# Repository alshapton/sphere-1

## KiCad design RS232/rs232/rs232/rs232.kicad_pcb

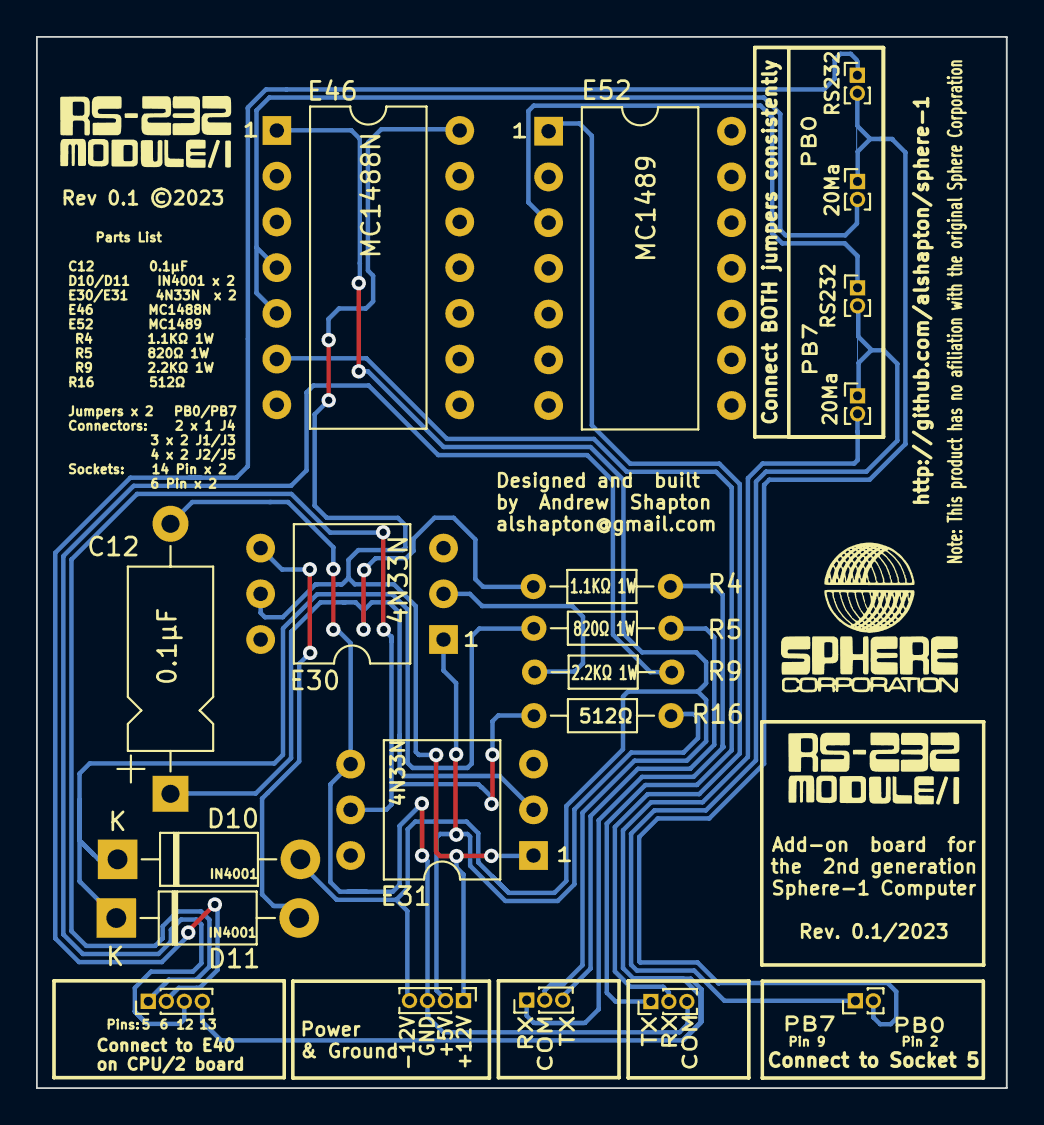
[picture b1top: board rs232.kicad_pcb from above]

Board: 2 copper layers, 53.9 x 58.4 mm, 20 parts (0 on the bottom side), 15 nets.

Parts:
C12: CK-104; CP_Axial_L10.0mm_D4.5mm_P15.00mm_Horizontal
D10, D11: 1N4001; D_DO-41_SOD81_P10.16mm_Horizontal
E30, E31: 4N33N; DIP-6_W10.16mm
E46: MC1488N; DIP-14_W10.16mm
E52: MC1489; DIP-14_W10.16mm
J1, J3: Conn_01x03_Pin; PinHeader_1x03_P1.00mm_Vertical
J2, J5: Conn_01x04_Pin; PinHeader_1x04_P1.00mm_Vertical
J4: Conn_01x02_Pin; PinHeader_1x02_P1.00mm_Vertical
R4: 1.1 kOhm 1W; R_Axial_DIN0204_L3.6mm_D1.6mm_P7.62mm_Horizontal
R5: 820 Ohm 1W; R_Axial_DIN0204_L3.6mm_D1.6mm_P7.62mm_Horizontal
R9: 2 kOhm ¼W; R_Axial_DIN0204_L3.6mm_D1.6mm_P7.62mm_Horizontal
R16: 512 Ohm ¼W; R_Axial_DIN0204_L3.6mm_D1.6mm_P7.62mm_Horizontal
TSC1, TSC2, TSC3, TSC4: PinHeader_1x02_P1.00mm_Vertical

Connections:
unnamed: C12.1, E31.2 (C), R4.1
unnamed: D10.2 (A), E46.1 (V_{CC}-), J1.2, J2.4
unnamed: D10.1 (K), D11.1 (K), R5.1
unnamed: D11.2 (A), E30.4 (E)
unnamed: E30.1 (A), J2.2, R16.2
unnamed: E30.2 (C), R9.1
unnamed: E30.5 (C), E31.1 (A), E46.14 (V_{CC}+), J2.1
unnamed: C12.2, E31.4 (E), J2.3, J3.3
unnamed: E46.4 (2A), E46.5 (2B)
unnamed: E46.6 (2Y), J3.1
unnamed: E52.1 (1A), J3.2
unnamed: J1.1, R4.2
unnamed: J1.3, R5.2
unnamed: E31.5 (C), J5.1, R16.1
unnamed: J5.3, R9.2

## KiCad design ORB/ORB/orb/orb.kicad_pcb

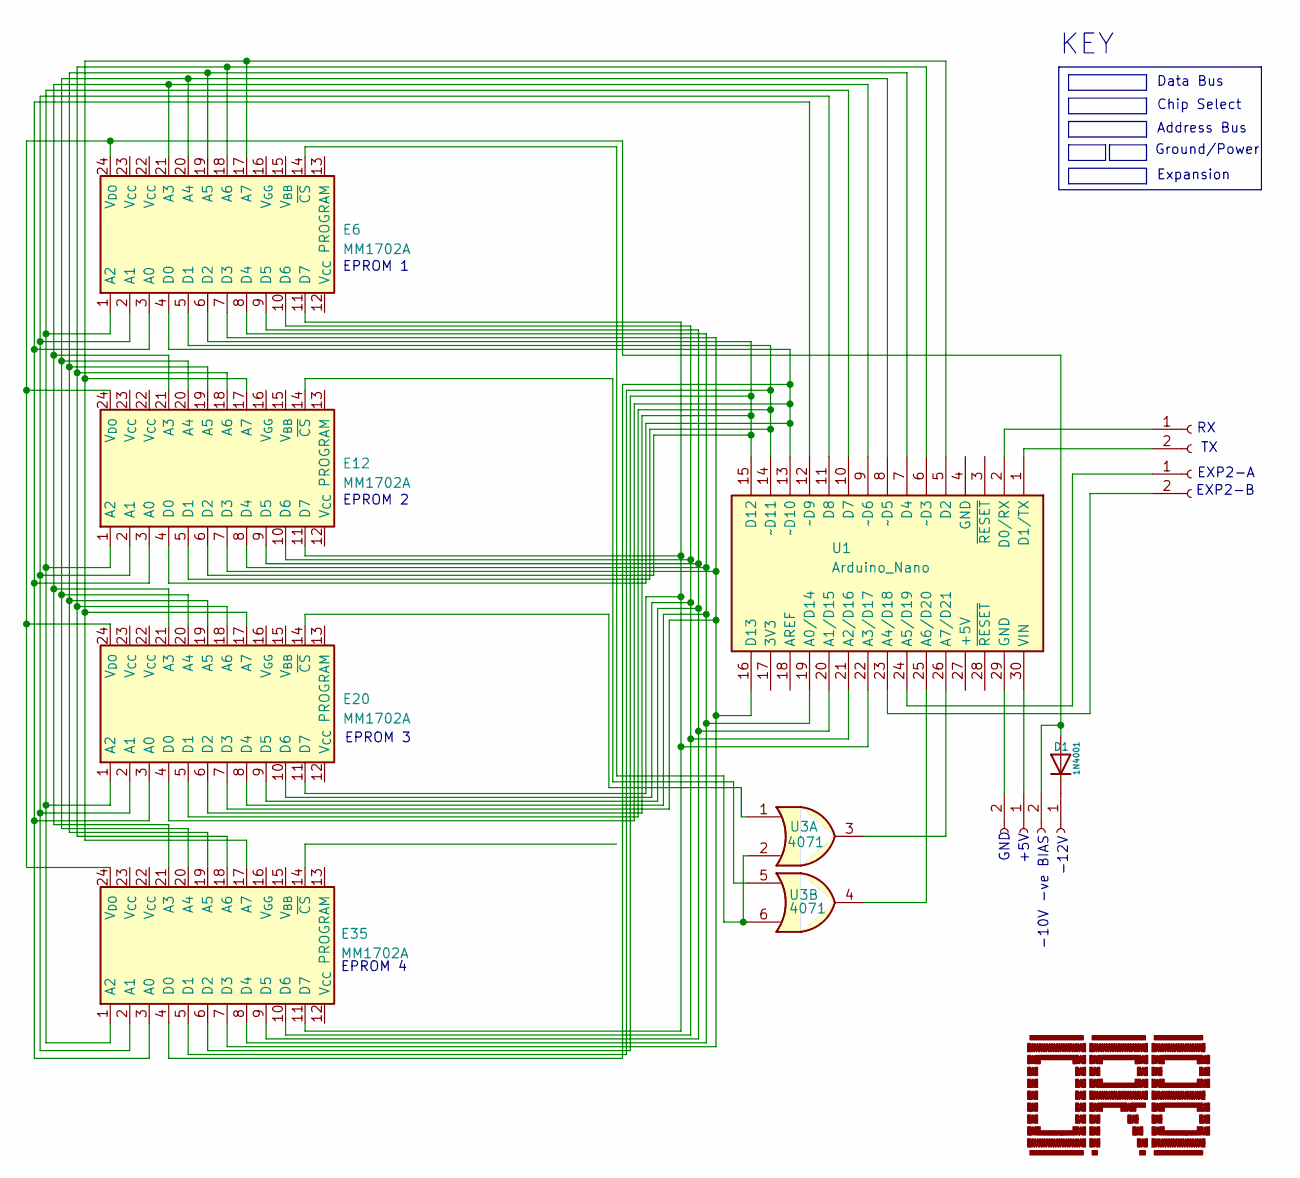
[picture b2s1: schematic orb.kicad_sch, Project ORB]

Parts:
D1: 1N4001; D_DO-41_SOD81_P10.16mm_Horizontal
E6, E12, E20, E35: MM1702A; DIP-24_W10.16mm_Socket
J1, J2, J3, J4: Conn_01x02_Socket; PinHeader_1x02_P1.00mm_Vertical
U1: Arduino_Nano
U3: 4071; PinSocket_2x07_P1.27mm_Vertical

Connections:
unnamed: D1.2 (A), E6.24 (V_{DO}), E12.24 (V_{DO}), E20.24 (V_{DO}), E35.24 (V_{DO}), J4.2
unnamed: D1.1 (K), J4.1
unnamed: E6.14 (~CS), U3.2, U3.6
unnamed: E6.3 (A0), E12.3 (A0), E20.3 (A0), E35.3 (A0), U1.12 (~D9)
unnamed: E6.2 (A1), E12.2 (A1), E20.2 (A1), E35.2 (A1), U1.11 (D8)
unnamed: E6.1 (A2), E12.1 (A2), E20.1 (A2), E35.1 (A2), U1.10 (D7)
unnamed: E6.21 (A3), E12.21 (A3), E20.21 (A3), E35.21 (A3), U1.9 (~D6)
unnamed: E6.20 (A4), E12.20 (A4), E20.20 (A4), E35.20 (A4), U1.8 (~D5)
unnamed: E6.19 (A5), E12.19 (A5), E20.19 (A5), E35.19 (A5), U1.7 (D4)
unnamed: E6.18 (A6), E12.18 (A6), E20.18 (A6), E35.18 (A6), U1.6 (~D3)
unnamed: E6.17 (A7), E12.17 (A7), E20.17 (A7), E35.17 (A7), U1.5 (D2)
unnamed: E6.4 (D0), E12.4 (D0), E20.4 (D0), E35.4 (D0), U1.13 (~D10)
unnamed: E6.5 (D1), E12.5 (D1), E20.5 (D1), E35.5 (D1), U1.14 (~D11)
unnamed: E6.6 (D2), E12.6 (D2), E20.6 (D2), E35.6 (D2), U1.15 (D12)
unnamed: E6.7 (D3), E12.7 (D3), E20.7 (D3), E35.7 (D3), U1.16 (D13)
unnamed: E6.8 (D4), E12.8 (D4), E20.8 (D4), E35.8 (D4), U1.19 (A0/D14)
unnamed: E6.9 (D5), E12.9 (D5), E20.9 (D5), E35.9 (D5), U1.20 (A1/D15)
unnamed: E6.10 (D6), E12.10 (D6), E20.10 (D6), E35.10 (D6), U1.21 (A2/D16)
unnamed: E6.11 (D7), E12.11 (D7), E20.11 (D7), E35.11 (D7), U1.22 (A3/D17)
unnamed: E12.14 (~CS), U3.5
unnamed: E20.14 (~CS), U3.1
unnamed: J1.1, U1.30 (VIN)
unnamed: J1.2, U1.29 (GND)
unnamed: J2.1, U1.2 (D0/RX)
unnamed: J2.2, U1.1 (D1/TX)
unnamed: J3.1, U1.24 (A5/D19)
unnamed: J3.2, U1.23 (A4/D18)
unnamed: U1.25 (A6/D20), U3.4
unnamed: U1.26 (A7/D21), U3.3

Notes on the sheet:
EPROM 2
-12V
-10V -ve BIAS
Data Bus
KEY
EPROM 3
EXP2-A
EXP2-B
Expansion
GND
Address Bus
EPROM 4
Ground/Power
EPROM 1
Chip Select
+5V

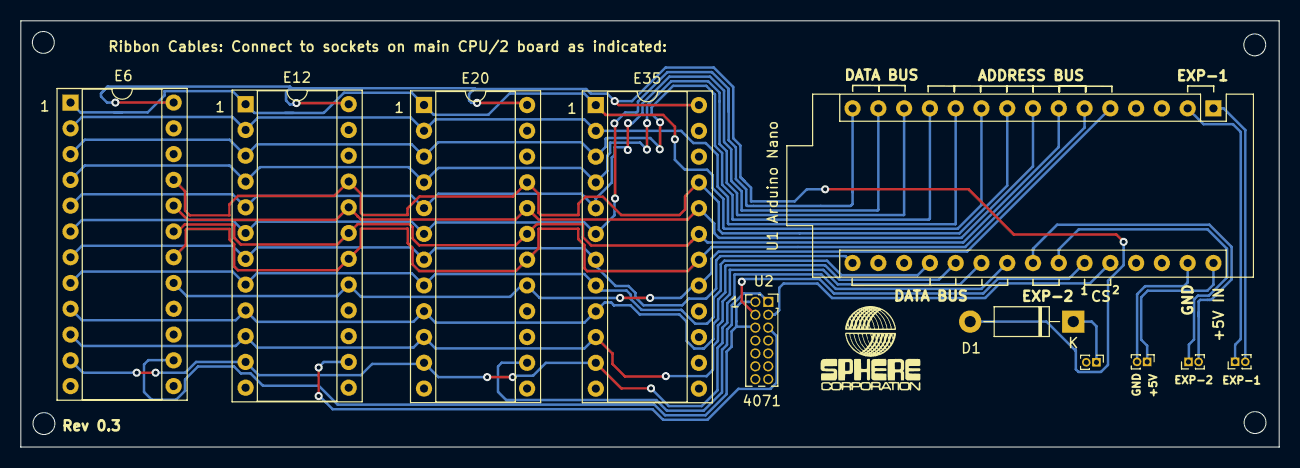
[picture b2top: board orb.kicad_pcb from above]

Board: 2 copper layers, 124.0 x 42.0 mm, 11 parts (0 on the bottom side), 29 nets.

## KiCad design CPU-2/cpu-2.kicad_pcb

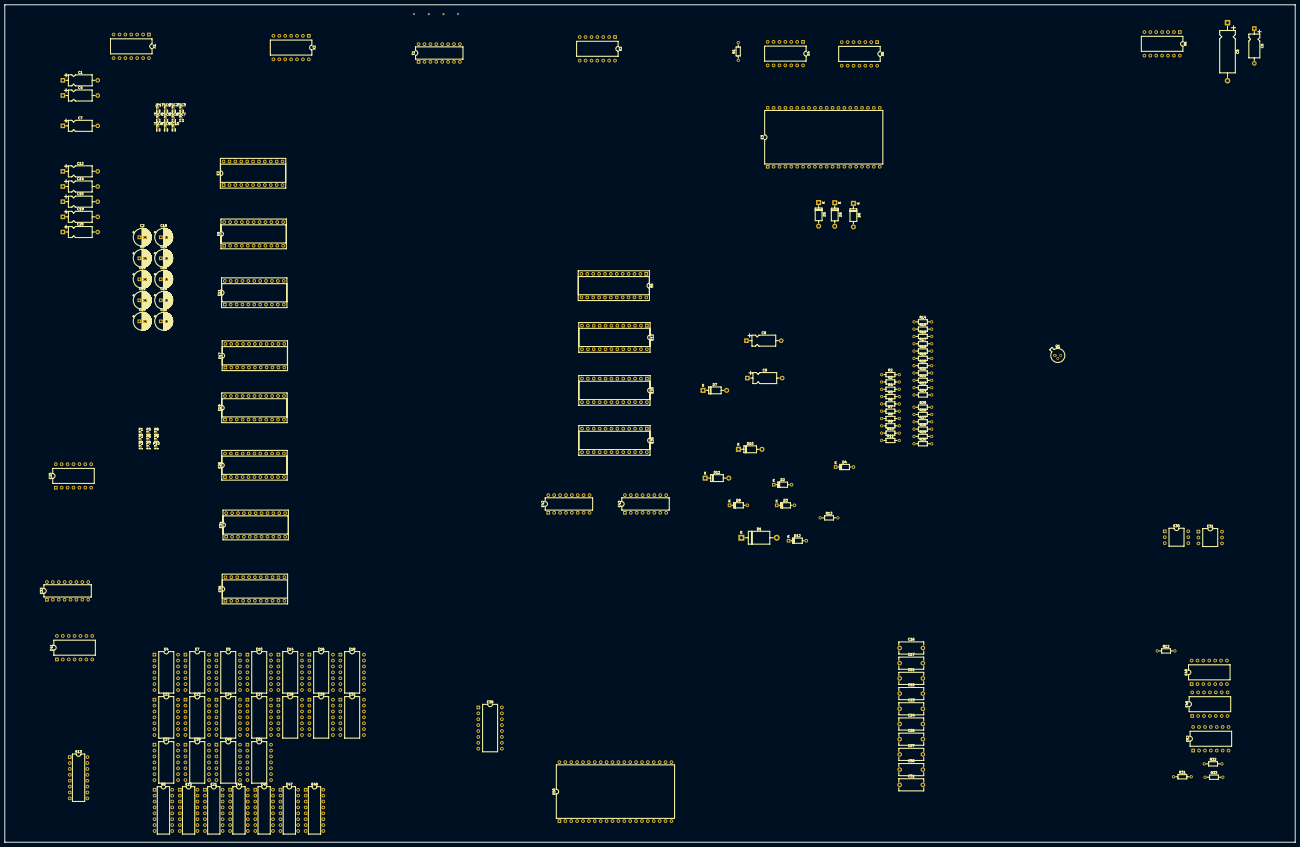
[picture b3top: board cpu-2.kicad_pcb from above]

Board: 2 copper layers, 556.0 x 360.8 mm, 156 parts (0 on the bottom side), 189 nets, no tracks yet.

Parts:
C1, C4, C6, C7, C8, C9, C12, C14, C15, C19, C20: CK-104; CP_Axial_L10.0mm_D4.5mm_P15.00mm_Horizontal
C2: _{EK47/16}; CP_Radial_D7.5mm_P2.50mm
C3, C10, C11, C13, C18, C25, C28, C29, C32: EK47/16; CP_Radial_D7.5mm_P2.50mm
C5: Tantalum Capacitor; CP_Axial_L18.0mm_D6.5mm_P25.00mm_Horizontal
C16: DDM-103'; C_Disc_D10.5mm_W5.0mm_P10.00mm
C17, C22, C23: DDM-103; C_Disc_D10.5mm_W5.0mm_P10.00mm
C21, C27, C31: DD-101; C_Disc_D10.5mm_W5.0mm_P10.00mm
C24, C30: DD-680; C_Disc_D10.5mm_W5.0mm_P10.00mm
C26: _{DDM-103'}; C_Disc_D10.5mm_W5.0mm_P10.00mm
D1: 1N5225B; D_DO-201AE_P15.24mm_Horizontal
D2, D3, D4, D9, D12: 1N914; D_DO-35_SOD27_P7.62mm_Horizontal
D5, D6, D7, D8, D10, D11: 1N4001; D_DO-41_SOD81_P10.16mm_Horizontal
E1, E33: DM8098N; DIP-16_W7.62mm
E2, E5, E11, E17, E19, E26, E34, E36: TMS4030; DIP-22_W10.16mm_Socket
E3: MC6820; DIP-40_W25.4mm
E4, E24: SN7420N; DIP-14_W10.16mm
E6, E12, E20, E35: MM1702A; DIP-24_W10.16mm_Socket
E7, E22, E27: SN7493N; DIP-14_W10.16mm
E8, E45: DM9602N; DIP-16_W7.62mm
E9, E37: SN7474N; DIP-14_W10.16mm
E10, E16, E23: SN7402N; DIP-14_W10.16mm
E13: SN7442N; DIP-16_W7.62mm
E14, E18: SN7411N; DIP-14_W10.16mm
E15, E21, E44, E47, E48: DM8097N; DIP-16_W7.62mm
E25: (SPARE); DIP-14_W10.16mm
E28: SN7408N; DIP-14_W10.16mm
E29: SN7404N; DIP-14_W10.16mm
E30, E31: 4N33N; DIP-6_W10.16mm
E32, E39: SN7400N; DIP-14_W10.16mm
E38: SN74123N; DIP-16_W10.16mm
E40, E41: SN7405N; DIP-14_W10.16mm
E42, E43: DM8833N; DIP-16_W7.62mm
E46: MC1488N; DIP-14_W10.16mm
E49: SN7486N; DIP-14_W10.16mm
E50: MC6800; DIP-40_W25.4mm
E51: MPQ6842; DIP-14_W10.16mm
E52: MC1489; DIP-14_W10.16mm
JP1: Jumper_Open; PinHeader_1x02_P1.00mm_Vertical
P1, P2, P3, P5, P6, P7, P8, P9, P10: PinHeader_1x01_P1.00mm_Vertical
Q1: 2N2369A; TO-18-3_Lens
R1: 100 Ohm ¼W; R_Axial_DIN0204_L3.6mm_D1.6mm_P7.62mm_Horizontal
R2, R3: 36 kOhm ¼W; R_Axial_DIN0204_L3.6mm_D1.6mm_P7.62mm_Horizontal
R4: 1.1 kOhm 1W; R_Axial_DIN0204_L3.6mm_D1.6mm_P7.62mm_Horizontal
R5: 820 Ohm 1W; R_Axial_DIN0204_L3.6mm_D1.6mm_P7.62mm_Horizontal
R6: 130 Ohm 2W; R_Axial_DIN0204_L3.6mm_D1.6mm_P7.62mm_Horizontal
R7, R8, R18, R20, R29: 3.3 kOhm ¼W; R_Axial_DIN0204_L3.6mm_D1.6mm_P7.62mm_Horizontal
R9: 2 kOhm ¼W; R_Axial_DIN0204_L3.6mm_D1.6mm_P7.62mm_Horizontal
R10: 15 kOhm ¼W; R_Axial_DIN0204_L3.6mm_D1.6mm_P7.62mm_Horizontal
R11: 27.1 kOhm ¼W; R_Axial_DIN0204_L3.6mm_D1.6mm_P7.62mm_Horizontal
R12: 11 kOhm ¼W; R_Axial_DIN0204_L3.6mm_D1.6mm_P7.62mm_Horizontal
R13: 33 kOhm ¼W; R_Axial_DIN0204_L3.6mm_D1.6mm_P7.62mm_Horizontal
R14: Resistor (R14); R_Axial_DIN0204_L3.6mm_D1.6mm_P7.62mm_Horizontal
R15, R33: 470 Ohm ¼W; R_Axial_DIN0204_L3.6mm_D1.6mm_P7.62mm_Horizontal
R16: 512 Ohm ¼W; R_Axial_DIN0204_L3.6mm_D1.6mm_P7.62mm_Horizontal
R17, R19, R31, R32: 1 kOhm ¼W; R_Axial_DIN0204_L3.6mm_D1.6mm_P7.62mm_Horizontal
R21, R28, R30: 10 kOhm ¼W; R_Axial_DIN0204_L3.6mm_D1.6mm_P7.62mm_Horizontal
R22, R25: 22 Ohm ¼W; R_Axial_DIN0204_L3.6mm_D1.6mm_P7.62mm_Horizontal
R23, R26: 10 Ohm ¼W; R_Axial_DIN0204_L3.6mm_D1.6mm_P7.62mm_Horizontal
R24, R27: 4.7 kOhm ¼W; R_Axial_DIN0204_L3.6mm_D1.6mm_P7.62mm_Horizontal
TSC1, TSC2, TSC3, TSC4, TSC5, TSC6, TSC7, TSC8, TSC9, TSC10: PinHeader_1x02_P1.00mm_Vertical
X1, X2, X3, X4, X5, X6: 14-Pin Socket; DIP-14_W10.16mm

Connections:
+5V: C5.1, C28.1, D12.1 (K), E2.11 (V_{CC}), E3.25 (ENABLE), E4.7 (GND), E5.11 (V_{CC}), E8.3 (CLR1), E8.13 (CLR2), E9.1 (1~CLR), E9.4 (1~PRE), E9.10 (2~PRE), E9.12 (2D), E10.7 (GND), E11.11 (V_{CC}), E14.13 (1C), E15.9 (Y4), E16.7 (GND), E17.11 (V_{CC}), E18.7 (GND), E19.11 (V_{CC}), E24.2 (1B), E24.7 (GND), E26.11 (V_{CC}), E30.1 (A), E32.7 (GND), E32.12 (4B), E34.11 (V_{CC}), E36.11 (V_{CC}), E37.1 (1~CLR), E37.4 (1~PRE), E37.10 (2~PRE), E37.12 (2D), E38.2 (1B), E38.3 (1~CLR), E38.10 (2B), E38.11 (2~CLR), E41.7 (GND), E45.3 (CLR1), E45.5 (A1), E45.11 (A2), E45.13 (CLR2), E49.7 (GND), E49.13 (4B), E50.8 (V_{CC}), E51.5, E51.10, R2.2, R3.1, R7.1, R10.2, R11.2, R12.2, R13.2, R14.2, R15.1, R16.2, R17.2, R18.1, R19.2, R28.1, R31.1, R32.2, R33.1, X1.14, X5.7, X5.14, X6.6, X6.7, X6.13, X6.14
+12V: C3.1, C10.1, C11.1, C13.1, C18.1, D9.1 (K), E2.18 (V_{DD}), E5.18 (V_{DD}), E11.18 (V_{DD}), E17.18 (V_{DD}), E19.18 (V_{DD}), E26.18 (V_{DD}), E30.5 (C), E31.1 (A), E34.18 (V_{DD}), E36.18 (V_{DD}), E46.14 (V_{CC}+), R6.1, X6.10
-3V3: C2.1, D1.2 (A2), D3.2 (A), E2.1 (V_{BB}), E5.1 (V_{BB}), E11.1 (V_{BB}), E17.1 (V_{BB}), E19.1 (V_{BB}), E26.1 (V_{BB}), E34.1 (V_{BB}), E36.1 (V_{BB}), X6.4, X6.11
-12V: D10.2 (A), E46.1 (V_{CC}-)
/A_{0}: E2.8 (A0), E5.8 (A0), E6.3 (A0), E11.8 (A0), E12.3 (A0), E16.3 (1B), E17.8 (A0), E19.8 (A0), E20.3 (A0), E21.13 (Y6), E26.8 (A0), E34.8 (A0), E35.3 (A0), E36.8 (A0), X2.8
/A_{1}: E2.9 (A1), E5.9 (A1), E6.2 (A1), E11.9 (A1), E12.2 (A1), E16.2 (1A), E17.9 (A1), E19.9 (A1), E20.2 (A1), E21.9 (Y4), E26.9 (A1), E34.9 (A1), E35.2 (A1), E36.9 (A1), X2.9
/A_{2}: E2.10 (A2), E5.10 (A2), E6.1 (A2), E11.10 (A2), E12.1 (A2), E17.10 (A2), E19.10 (A2), E20.1 (A2), E21.7 (Y3), E24.9 (2A), E26.10 (A2), E34.10 (A2), E35.1 (A2), E36.10 (A2), X2.1
/A_{3}: E2.13 (A3), E5.13 (A3), E6.21 (A3), E10.5 (2A), E11.13 (A3), E12.21 (A3), E17.13 (A3), E19.13 (A3), E20.21 (A3), E21.2 (A1), E21.3 (Y1), E22.14 (CKA), E26.13 (A3), E27.11 (Q_{D}), E34.13 (A3), E35.21 (A3), E36.13 (A3), X2.3
/A_{4}: E2.14 (A4), E5.14 (A4), E6.20 (A4), E10.8 (3A), E11.14 (A4), E12.20 (A4), E17.14 (A4), E19.14 (A4), E20.20 (A4), E21.11 (Y5), E26.14 (A4), E34.14 (A4), E35.20 (A4), E36.14 (A4), X2.2
/A_{5}: E2.15 (A5), E5.15 (A5), E6.19 (A5), E10.6 (2B), E11.15 (A5), E12.19 (A5), E17.15 (A5), E19.15 (A5), E20.19 (A5), E21.5 (Y3), E26.15 (A5), E34.15 (A5), E35.19 (A5), E36.15 (A5), X2.4
/A_{6}: E2.19 (A6), E5.19 (A6), E6.18 (A6), E11.19 (A6), E12.18 (A6), E17.19 (A6), E19.19 (A6), E20.18 (A6), E26.19 (A6), E34.19 (A6), E35.18 (A6), E36.19 (A6), X2.5
/A_{7}: E2.20 (A7), E5.20 (A7), E6.17 (A7), E10.9 (3B), E11.20 (A7), E12.17 (A7), E17.20 (A7), E19.20 (A7), E20.17 (A7), E26.20 (A7), E34.20 (A7), E35.17 (A7), E36.20 (A7), X2.6
/A_{8}: E2.21 (A9), E5.21 (A9), E10.11 (4A), E11.21 (A9), E13.15 (A), E17.21 (A9), E19.21 (A9), E26.21 (A9), E34.21 (A9), E36.21 (A9), X2.7
/A_{9}: E2.2 (A9), E5.2 (A9), E10.12 (4B), E11.2 (A9), E13.14 (B), E17.2 (A9), E19.2 (A9), E26.2 (A9), E34.2 (A9), E36.2 (A9), X1.2
/A_{10}: E2.3 (A10), E4.1 (1A), E5.3 (A10), E10.2 (1A), E11.3 (A10), E17.3 (A10), E19.3 (A10), E26.3 (A10), E34.3 (A10), E36.3 (A10), X1.13
/A_{11}: E2.4 (A11), E4.2 (1B), E5.4 (A11), E10.3 (1B), E11.4 (A11), E17.4 (A11), E18.3 (2A), E19.4 (A11), E26.4 (A11), E34.4 (A11), E36.4 (A11), X1.12
/A_{12}: E4.13 (2D), E16.11 (4A), X1.11
/A_{13}: E4.12 (2C), E16.9 (3B), X1.10
/A_{14}: E4.10 (2B), E16.12 (4B), X1.4
/A_{15}: E4.9 (2A), E16.8 (3A), X1.5
/D_{0}: E1.3 (Y1), E2.6 (DI), E3.33 (D0), E6.4 (D0), E20.4 (D0), E35.4 (D0), E43.15 (B_{D}), X3.7
/D_{1}: E1.13 (Y6), E3.32 (D1), E5.6 (DI), E6.5 (D1), E20.5 (D1), E35.5 (D1), E43.1 (BUS_{A}), X3.8
/D_{2}: E1.5 (Y3), E3.31 (D2), E6.6 (D2), E11.6 (DI), E20.6 (D2), E35.6 (D2), E43.4 (BUS_{B}), X3.6
/D_{3}: E1.11 (Y5), E3.30 (D3), E6.7 (D3), E17.6 (DI), E20.7 (D3), E35.7 (D3), E43.12 (B_{C}), X3.5
/D_{4}: E1.7 (Y3), E3.29 (D4), E6.8 (D4), E19.6 (DI), E20.8 (D4), E35.8 (D4), E42.1 (BUS_{A}), X3.1
/D_{5}: E1.9 (Y4), E3.28 (D5), E6.9 (D5), E20.9 (D5), E26.6 (DI), E35.9 (D5), E42.15 (B_{D}), X3.13
/D_{6}: E3.27 (D6), E6.10 (D6), E20.10 (D6), E33.9 (Y4), E34.6 (DI), E35.10 (D6), E42.4 (BUS_{B}), X3.14
/D_{7}: E3.26 (D7), E6.11 (D7), E20.11 (D7), E33.5 (Y3), E35.11 (D7), E36.6 (DI), E42.12 (B_{C}), X3.2
/_{A6}: E3.22 (CS0), E24.12 (2C)
/_{CE}: E2.17 (CE), E5.17 (CE), E11.17 (CE), E17.17 (CE), E19.17 (CE), E26.17 (CE), E34.17 (CE), E36.17 (CE)
/_{RW}: E2.12 (R/~W), E4.5 (1D), E5.12 (R/~W), E11.12 (R/~W), E14.2 (1B), E17.12 (R/~W), E19.12 (R/~W), E26.12 (R/~W), E29.13 (6A), E32.5 (2B), E34.12 (R/~W), E36.12 (R/~W), X1.1
/_{TRI-S}: E1.1 (~G1), E1.15 (~G2), E33.1 (~G1), E33.15 (~G2)
/_{VMA}: E14.1 (1A), E24.1 (1A), E32.13 (4A), X1.3
/_{~CS}: E2.5 (~CS), E5.5 (~CS), E11.5 (~CS), E17.5 (~CS), E19.5 (~CS), E26.5 (~CS), E34.5 (~CS), E36.5 (~CS)
/_{~HLT}: E39.9 (3B), R7.2
/_{~IRQ }: E3.37 (~IRQB), E3.38 (~IRQA)
GNDREF: C2.2, C3.2, C5.2, C10.2, C11.2, C12.2, C13.2, C18.2, C26.2, C29.2, C32.2, D1.1 (A1), D3.1 (K), D4.1 (K), D9.2 (A), E2.22 (V_{SS}), E3.1 (VSS), E5.22 (V_{SS}), E8.4 (B1), E8.12 (B2), E11.22 (V_{SS}), E13.13 (C), E15.1 (~G1), E15.15 (~G2), E17.22 (V_{SS}), E19.22 (V_{SS}), E26.22 (V_{SS}), E31.4 (E), E34.22 (V_{SS}), E36.22 (V_{SS}), E44.1 (~G1), E44.15 (~G2), E47.1 (~G1), E47.15 (~G2), E50.1 (V_{SS}), E50.21 (V_{SS}), E50.39 (TSC), E51.3, E51.12, Q1.1 (E), X4.8, X5.8, X6.1, X6.2, X6.8, X6.9
unnamed: C12.1, E31.2 (C), R4.1
unnamed: C24.1, E51.13, R21.2
unnamed: C27.1, E51.9, R24.2, R31.2
unnamed: C28.2, C32.1
unnamed: C30.1, E51.2, R30.2
unnamed: C31.1, E51.6, R27.2, R32.1
unnamed: D4.2 (A), D7.1 (K), X6.12
unnamed: D5.2 (A), D8.1 (K)
unnamed: D5.1 (K), D6.2 (A)
unnamed: D6.1 (K), D7.2 (A)
unnamed: D10.1 (K), D11.1 (K), R5.1
unnamed: D11.2 (A), E30.4 (E)
unnamed: C29.1, D12.2 (A), E49.12 (4A), R28.2
unnamed: E1.2 (A1), E2.7 (~DO)
unnamed: E1.4 (A2), E11.7 (~DO)
unnamed: E1.6 (A3), E19.7 (~DO)
unnamed: E1.10 (A4), E26.7 (~DO)
unnamed: E1.12 (A5), E17.7 (~DO)
unnamed: E1.14 (A6), E5.7 (~DO)
unnamed: E3.39 (CA2), X4.12
unnamed: E3.18 (CB1), X5.13
unnamed: E3.19 (CB2), X5.12
unnamed: E3.2 (PA0), X4.2
unnamed: E3.3 (PA1), X4.3
unnamed: E3.4 (PA2), X4.11
unnamed: E3.5 (PA3), X4.4
unnamed: E3.6 (PA4), X4.10
unnamed: E3.7 (PA5), X4.5
unnamed: E3.8 (PA6), X4.6
unnamed: E3.9 (PA7), X4.9
unnamed: E3.10 (PB0), X5.2
unnamed: E3.11 (PB1), X5.3
unnamed: E3.12 (PB2), X5.11
unnamed: E3.13 (PB3), X5.4
unnamed: E3.14 (PB4), X5.10
unnamed: E3.15 (PB5), X5.5
unnamed: E3.16 (PB6), X5.6
unnamed: E3.17 (PB7), X5.9
unnamed: E3.20 (V_{CC}), X4.7
unnamed: E3.34 (~RESET), X4.1, X5.1
unnamed: E7.1 (CKB), E7.12 (Q_{A})
unnamed: E8.5 (A1), E8.10 (Q2), E9.2 (1D)
unnamed: E8.6 (Q1), E8.11 (A2)
unnamed: C9.2, E8.1 (C_{ext}1)
unnamed: C8.2, E8.15 (C_{ext}2)
unnamed: C9.1, E8.2 (R_{ext}/C_{ext}1), R3.2
unnamed: C8.1, E8.14 (R_{ext}/C_{ext}2), R2.1
unnamed: E9.5 (1Q), E9.11 (2CLK)
unnamed: E10.1 (1Y), E18.1 (1A)
unnamed: E10.4 (2Y), E18.10 (3B)
unnamed: E10.10 (3Y), E18.9 (3A)
unnamed: E6.24 (V_{DO}), E12.24 (V_{DO}), E20.24 (V_{DO}), E35.24 (V_{DO})
unnamed: E12.14 (~CS), E13.2 (1)
unnamed: E6.14 (~CS), E13.1 (0)
unnamed: E13.3 (2), E20.14 (~CS)
unnamed: E4.6 (1Y), E13.12 (D)
unnamed: E14.12 (1Y), E29.3 (2A), E42.9 (OVR-DIS), E43.9 (OVR-DIS)
unnamed: E15.4 (A2), E28.3
unnamed: E15.10 (A4), E45.10 (Q2)
unnamed: E15.12 (A5), E45.6 (Q1)
unnamed: E15.5 (Y3), X3.4
unnamed: E9.3 (1CLK), E15.11 (Y5), E28.12, E37.3 (1CLK), E39.12 (4B)
unnamed: E15.13 (Y6), E22.2 (R0(1)), E22.3 (R0(2)), E23.2 (1A), E27.2 (R0(1)), E27.3 (R0(2)), E28.1, E39.10 (3A)
unnamed: E16.1 (1Y), E24.13 (2D)
unnamed: E16.5 (2A), E32.11 (4Y)
unnamed: E4.8 (2Y), E16.6 (2B)
unnamed: E4.4 (1C), E16.4 (2Y), E18.2 (1B)
unnamed: E16.10 (3Y), E24.5 (1D)
unnamed: E16.13 (4Y), E24.4 (1C)
unnamed: E18.8 (3Y), E18.13 (1C)
unnamed: E3.24 (CS1), E18.12 (1Y), E24.10 (2B)
unnamed: E21.6 (A3), E27.8 (Q_{C})
unnamed: E21.10 (A4), E27.9 (Q_{B})
unnamed: E21.12 (A5), E22.1 (CKB), E22.12 (Q_{A})
unnamed: E21.14 (A6), E27.1 (CKB), E27.12 (Q_{A})
unnamed: E21.1 (~G1), E21.15 (~G2), E29.8 (4Y)
unnamed: E22.8 (Q_{C}), E39.13 (4A)
unnamed: E23.3 (1B), E23.10 (3Y), E29.11 (5A)
unnamed: E7.14 (CKA), E23.1 (1Y), E29.9 (4A)
unnamed: E23.8 (3A), E37.9 (2Q)
unnamed: E23.9 (3B), E50.7 (BA)
unnamed: E24.6 (1Y), E28.10, E41.11 (5A)
unnamed: E27.14 (CKA), E28.11
unnamed: E28.6, E29.1 (1A)
unnamed: E29.4 (2Y), E42.7 (REC-DIS), E43.7 (REC-DIS)
unnamed: E29.6 (3Y), X3.9
unnamed: E28.2, E28.13, E29.10 (5Y), E48.1 (~G1), E48.15 (~G2)
unnamed: E29.12 (6Y), E32.3 (1Y), E38.9 (2A)
unnamed: E30.2 (C), R9.2
unnamed: E28.5, E32.1 (1A)
unnamed: E32.2 (1B), E32.4 (2A), E41.10 (5Y), R19.1
unnamed: E32.10 (3A), E41.6 (3Y)
unnamed: E7.2 (R0(1)), E7.3 (R0(2)), E32.8 (3Y)
unnamed: E33.4 (A2), E36.7 (~DO)
unnamed: E33.10 (A4), E34.7 (~DO)
unnamed: E37.2 (1D), E39.8 (3Y)
unnamed: E37.6 (1~Q), E38.1 (1A), E50.2 (~HALT)
unnamed: E37.11 (2CLK), E38.4 (1~Q)
unnamed: E37.13 (2~CLR), E39.11 (4Y)
unnamed: C16.2, E38.14 (1C_{ext})
unnamed: C16.1, E38.15 (1R_{ext}/C_{ext}), R10.1
unnamed: C21.2, E38.6 (2C_{ext})
unnamed: C21.1, E38.7 (2R_{ext}/C_{ext}), R13.1
unnamed: E28.4, E38.12 (2~Q)
unnamed: E31.5 (C), E40.5 (3A), R16.1
unnamed: E40.6 (3Y), R17.1
unnamed: E40.12 (6Y), R9.1
unnamed: E41.5 (3A), E49.11 (4Y)
unnamed: E42.2 (I_{A}), E42.3 (O_{A}), E50.29 (D4)
unnamed: E42.5 (I_{B}), E42.6 (O_{B}), E50.27 (D6)
unnamed: E42.10 (O_{C}), E42.11 (I_{C}), E50.26 (D7)
unnamed: E42.13 (O_{D}), E42.14 (I_{D}), E50.28 (D5)
unnamed: E43.2 (I_{A}), E43.3 (O_{A}), E50.32 (D1)
unnamed: E43.5 (I_{B}), E43.6 (O_{B}), E50.31 (D2)
unnamed: E43.10 (O_{C}), E43.11 (I_{C}), E50.30 (D3)
unnamed: E43.13 (O_{D}), E43.14 (I_{D}), E50.33 (D0)
unnamed: E44.2 (A1), E50.25 (A15)
unnamed: E44.4 (A2), E50.24 (A14)
unnamed: E44.6 (A3), E50.23 (A13)
unnamed: E44.10 (A4), E50.22 (A12)
unnamed: E44.12 (A5), E50.5 (VMA)
unnamed: E44.14 (A6), E50.34 (R/~W)
unnamed: C24.2, C27.2, E45.4 (B1), E45.9 (~Q2), R15.2, R21.1, R24.1
unnamed: C30.2, C31.2, E45.7 (~Q1), E45.12 (B2), R27.1, R30.1, R33.2
unnamed: C23.2, E45.1 (C_{ext}1)
unnamed: C22.1, E45.15 (C_{ext}2)
unnamed: C23.1, E45.2 (R_{ext}/C_{ext}1), R12.1
unnamed: C22.2, E45.14 (R_{ext}/C_{ext}2), R11.1, R14.1
unnamed: E46.4 (2A), E46.5 (2B)
unnamed: E47.2 (A1), E50.18 (A9)
unnamed: E47.4 (A2), E50.19 (A10)
unnamed: E47.6 (A3), E50.20 (A11)
unnamed: E47.10 (A4), E50.15 (A6)
unnamed: E47.12 (A5), E50.16 (A7)
unnamed: E47.14 (A6), E50.17 (A8)
unnamed: E48.2 (A1), E50.14 (A5)
unnamed: E48.4 (A2), E50.13 (A4)
unnamed: E48.6 (A3), E50.12 (A3)
unnamed: E48.10 (A4), E50.11 (A2)
unnamed: E48.12 (A5), E50.10 (A1)
unnamed: E48.14 (A6), E50.9 (A0)
unnamed: E50.36 (DBE), E50.37 (Phi2), R22.1, R23.2
unnamed: E50.3 (Phi1), R25.1, R26.2
unnamed: E50.4 (~IRQ), R20.2
unnamed: E50.6 (~NMI), R29.2
unnamed: C26.1, E50.40 (~RESET), R18.2
unnamed: E51.1, R26.1
unnamed: E51.7, R25.2
unnamed: E51.8, R22.2
unnamed: E51.14, R23.1
unnamed: E28.8, Q1.2 (B)
unnamed: Q1.3 (C), R6.2

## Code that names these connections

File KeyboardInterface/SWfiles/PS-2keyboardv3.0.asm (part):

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; DATA PORT to Apple 
;
	
	.EQU	BIT0_B0 	=	0x01 		; D0 ASCII bit - PB0
	.EQU	BIT0_B0_N	=	0

	.EQU	BIT1_B1		=	0x02		; D1 ASCII bit - PB1
	.EQU	BIT1_B1_N	=	1

	.EQU	BIT2_B2		=	0x04		; D2 ASCII bit - PB2
	.EQU	BIT2_B2_N	=	2

	.EQU	BIT3_B3		=	0x08		; D3 ASCII bit - PB3
	.EQU	BIT3_B3_N	=	3

	.EQU	BIT4_B4		=	0x10		; D4 ASCII bit - PB4
	.EQU	BIT4_B4_N	=	4

	.EQU	BIT5_B5		=	0x20		; D5 ASCII bit - PB5
	.EQU	BIT5_B5_N	=	5

	.EQU	BIT6_B6		=	0x40		; D6 ASCII bit - PB6
	.EQU	BIT6_B6_N	=	6

	.EQU	RESET_A0	=	0x01		; RESET - LOW resets motherboard - PA0
	.EQU	RESET_A0_N	=	0

	.EQU	STROBE_D3	=	0x08		; STROBE Rising edge indicates data available - PD3
	.EQU	STROBE_D3_N	=	3

	.EQU	CLEAR_A1	=	0x02		; CLEAR - HIGH clears Apple 1 screen -PA1
	.EQU	CLEAR_A1_N	=	1


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
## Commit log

2023-05-03 Added book file (LFS support required)
2023-05-05 Tidied up and added additional Project ORB documents + more KiCAD updates
2023-05-05 Added Project ORB documents and latest KiCAD updates
2023-05-05 Deleted extraneous documents
2023-05-05 CPU/2 Schematic updates
2023-05-18 More updates to schematics, books, created RS232 interface project
2023-05-18 Re-organised and tidied repo
2023-07-02 Latest updates

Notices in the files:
RS232/rs232/rs232/rs232.kicad_pcb:
Rev 0.1 ©2023
